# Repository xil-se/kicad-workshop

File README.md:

# Workshop example PCB

This PCB design is meant to be used as a reference for how to work with KiCad.

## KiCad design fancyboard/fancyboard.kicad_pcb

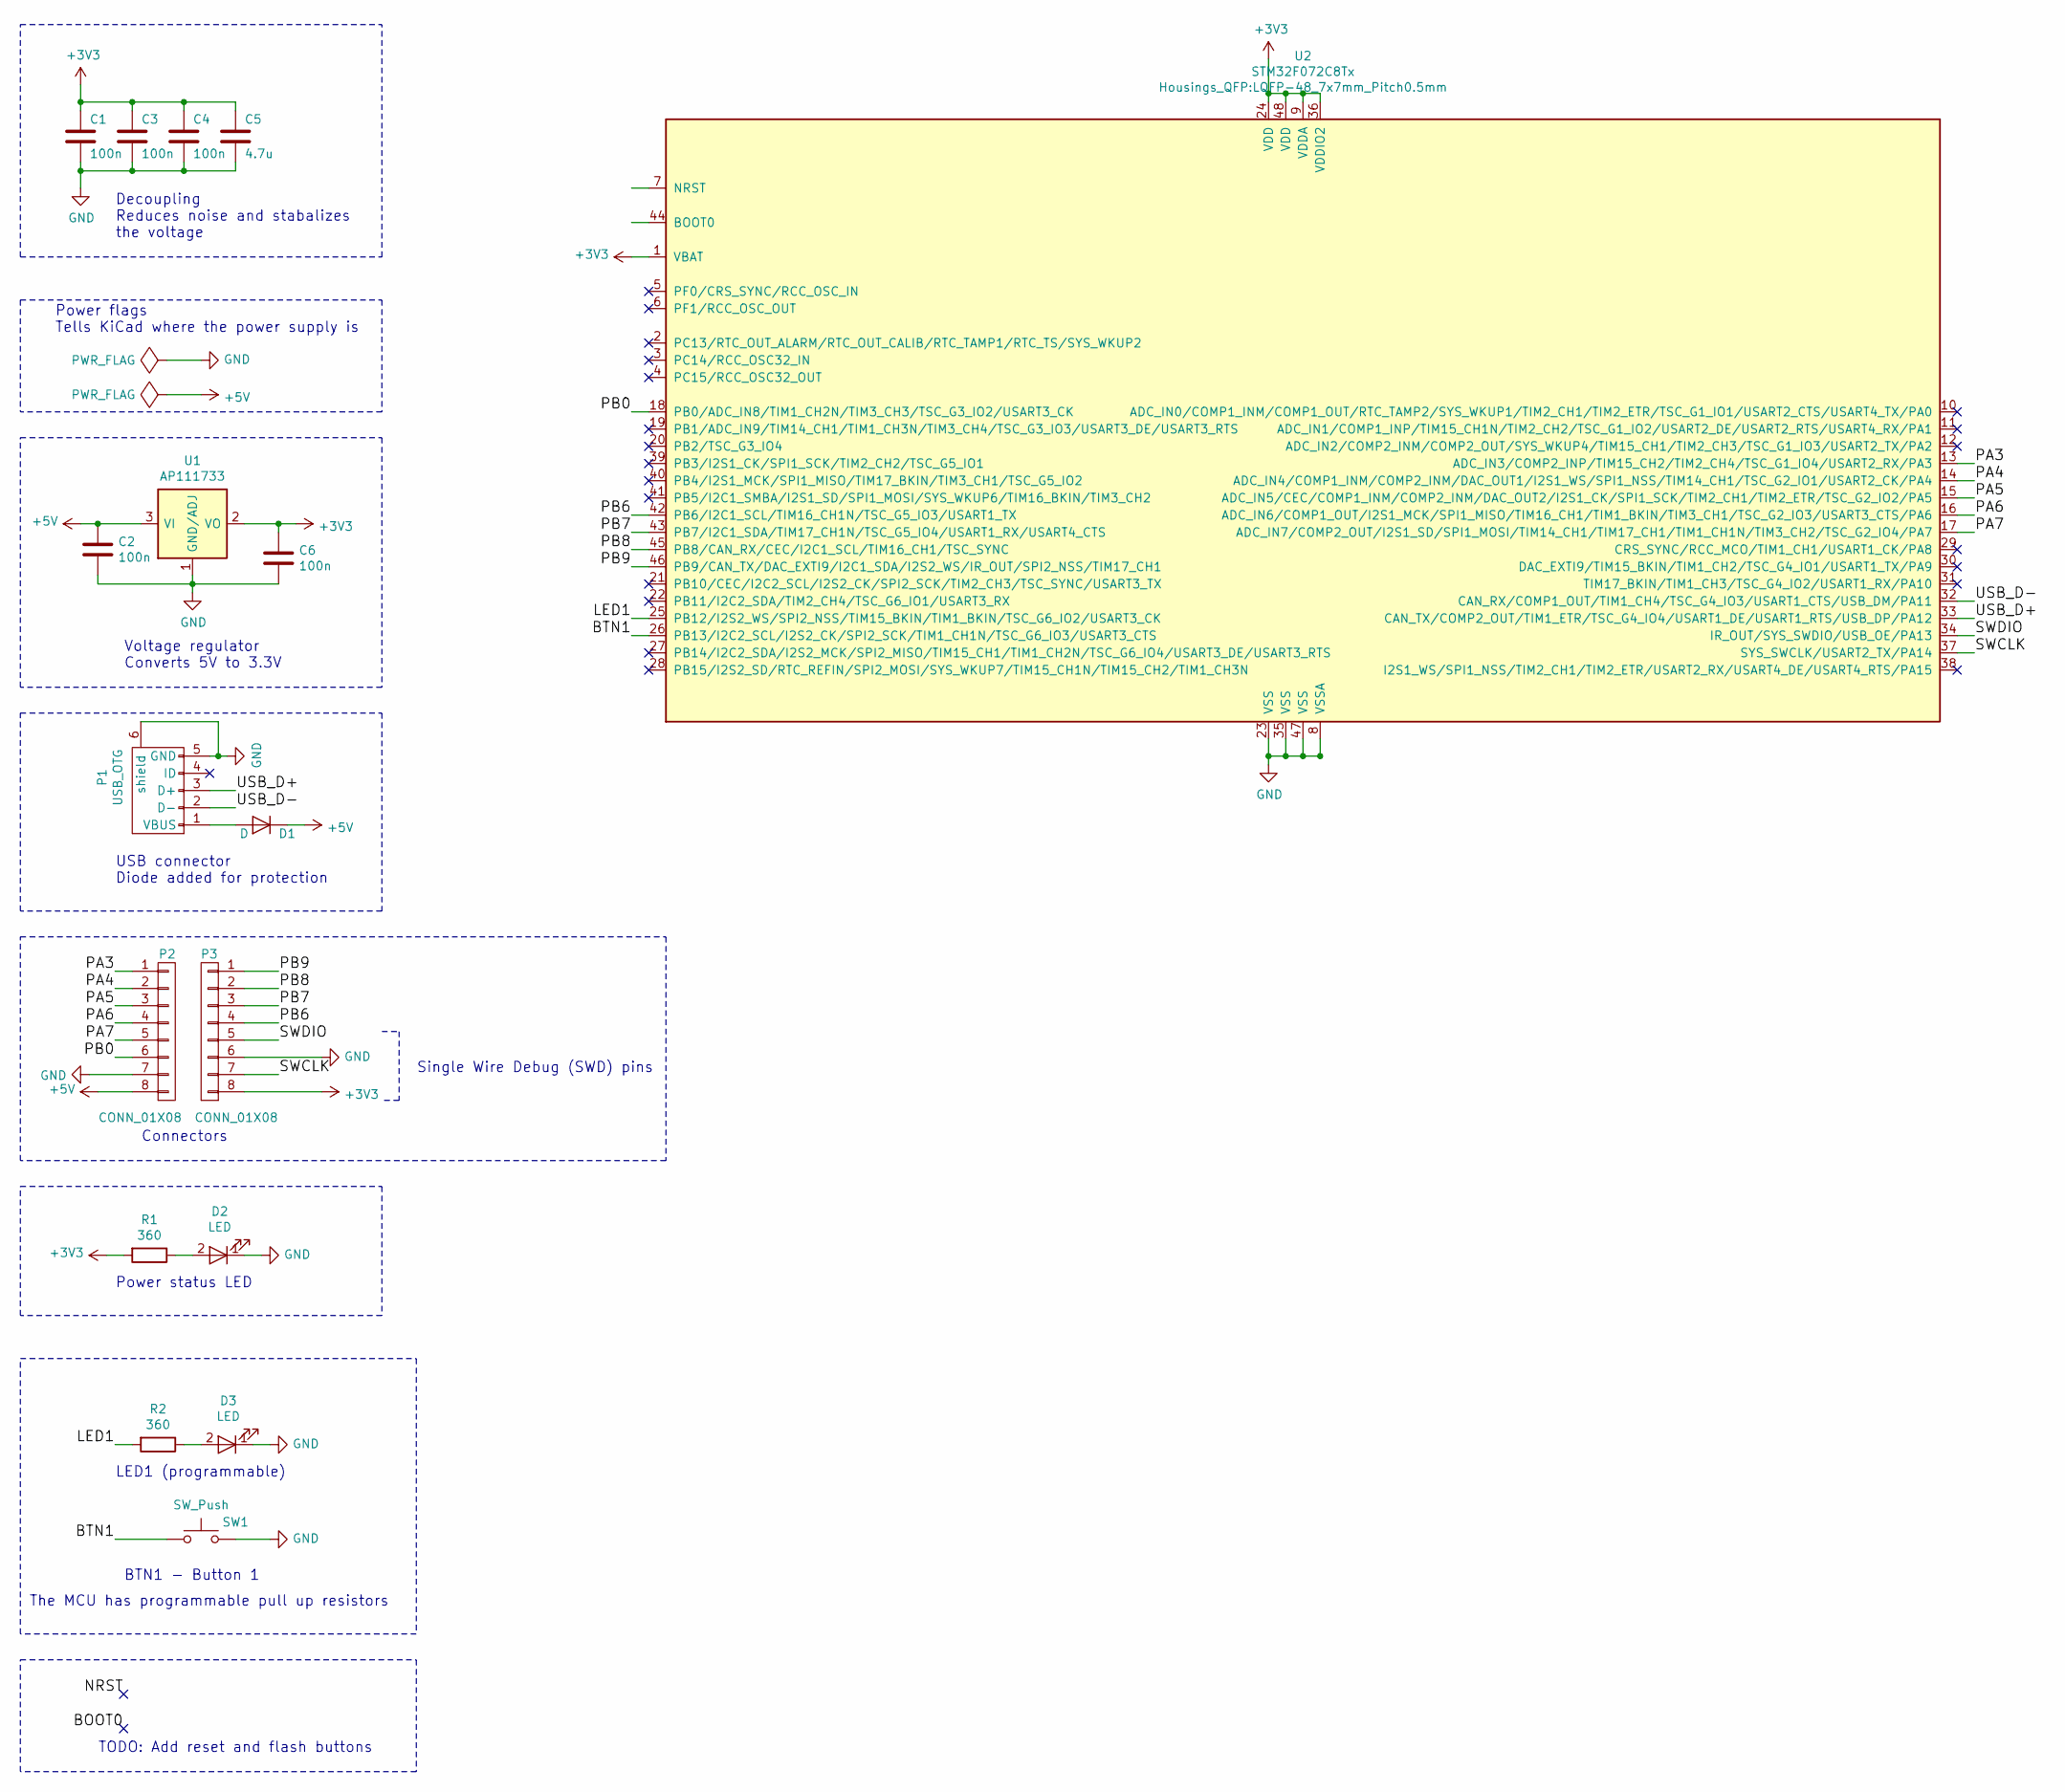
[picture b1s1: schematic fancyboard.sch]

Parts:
C1, C2, C3, C4, C6: 100n; C_0603
C5: 4.7u; C_0603
D1: D; SOD-323
D2, D3: LED; LED_0603
P1: USB_OTG; USB_Micro-B
P2, P3: CONN_01X08; Pin_Header_Straight_1x08
R1, R2: 360; R_0603
SW1: SW_Push; SmallButton
U1: AP111733; SOT-223
U2: STM32F072C8Tx; LQFP-48_7x7mm_Pitch0.5mm

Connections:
+3V3: C1.1, C3.1, C4.1, C5.1, C6.1, P3.8, R1.2, U1.2 (VO), U1.4 (VO), U2.1 (VBAT), U2.9 (VDDA), U2.24 (VDD), U2.36 (VDDIO2), U2.48 (VDD)
+5V: C2.1, D1.1 (K), P2.8, U1.3 (VI)
/BOOT0: U2.44 (BOOT0)
/BTN1: SW1.1, U2.26 (PB13/I2C2_SCL/I2S2_CK/SPI2_SCK/TIM1_CH1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)
/LED1: R2.2, U2.25 (PB12/I2S2_WS/SPI2_NSS/TIM15_BKIN/TIM1_B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)
/NRST: U2.7 (NRST)
/PA3: P2.1, U2.13 (ADC_IN3/COMP2_INP/TIM15_CH2/TIM2_CH4/TS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)
/PA4: P2.2, U2.14 (ADC_IN4/COMP1_INM/COMP2_INM/DAC_OUT1/I2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)
/PA5: P2.3, U2.15 (ADC_IN5/CEC/COMP1_INM/COMP2_INM/DAC_OUT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)
/PA6: P2.4, U2.16 (ADC_IN6/COMP1_OUT/I2S1_MCK/SPI1_MISO/TI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)
/PA7: P2.5, U2.17 (ADC_IN7/COMP2_OUT/I2S1_SD/SPI1_MOSI/TIM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)
/PB0: P2.6, U2.18 (PB0/ADC_IN8/TIM1_CH2N/TIM3_CH3/TSC_G3_I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)
/PB6: P3.4, U2.42 (PB6/I2C1_SCL/TIM16_CH1N/TSC_G5_IO3/USAR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)
/PB7: P3.3, U2.43 (PB7/I2C1_SDA/TIM17_CH1N/TSC_G5_IO4/USAR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)
/PB8: P3.2, U2.45 (PB8/CAN_RX/CEC/I2C1_SCL/TIM16_CH1/TSC_S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)
/PB9: P3.1, U2.46 (PB9/CAN_TX/DAC_EXTI9/I2C1_SDA/I2S2_WS/I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)
/SWCLK: P3.7, U2.37 (SYS_SWCLK/USART2_TX/PA14)
/SWDIO: P3.5, U2.34 (IR_OUT/SYS_SWDIO/USB_OE/PA13)
/USB_D+: P1.3 (D+), U2.33 (CAN_TX/COMP2_OUT/TIM1_ETR/TSC_G4_IO4/US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)
/USB_D-: P1.2 (D-), U2.32 (CAN_RX/COMP1_OUT/TIM1_CH4/TSC_G4_IO3/US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)
GND: C1.2, C2.2, C3.2, C4.2, C5.2, C6.2, D2.1 (K), D3.1 (K), P1.5 (GND), P1.6 (shield), P2.7, P3.6, SW1.2, U1.1 (GND/ADJ), U2.8 (VSSA), U2.23 (VSS), U2.35 (VSS), U2.47 (VSS)
unnamed: D1.2 (A), P1.1 (VBUS)
unnamed: D2.2 (A), R1.1
unnamed: D3.2 (A), R2.1

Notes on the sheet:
Decoupling Reduces noise and stabalizes the voltage
Power flags Tells KiCad where the power supply is
Voltage regulator Converts 5V to 3.3V
USB connector Diode added for protection
Connectors
Single Wire Debug (SWD) pins
Power status LED
LED1 (programmable)
BTN1 - Button 1
The MCU has programmable pull up resistors
TODO: Add reset and flash buttons

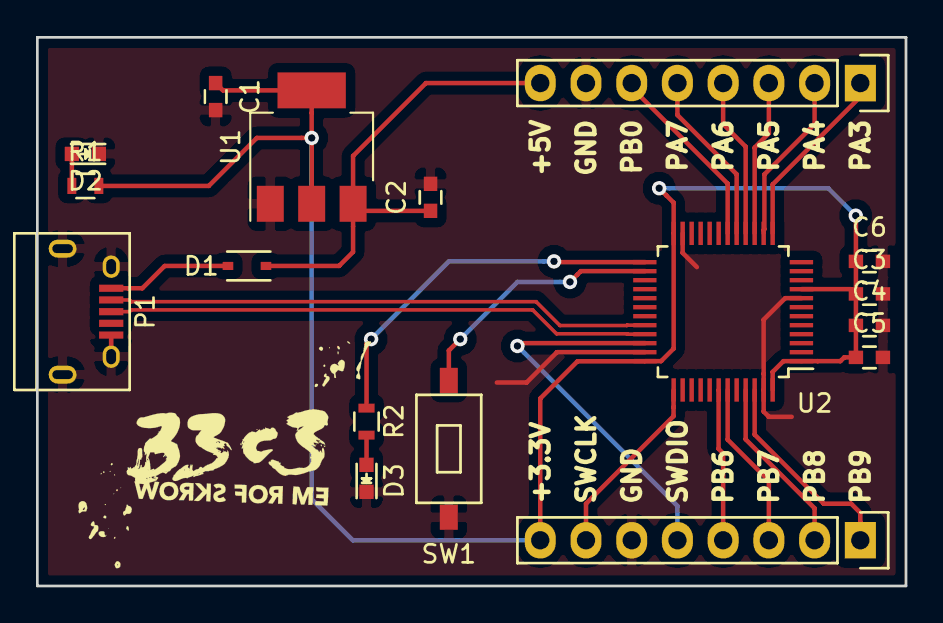
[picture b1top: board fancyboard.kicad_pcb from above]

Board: 2 copper layers, 48.3 x 30.5 mm, 17 parts (0 on the bottom side), 22 nets.

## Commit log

2016-12-27 KiCad Workshop project
2016-12-27 Support kicad-stable
    Removed diff_pair_gap and diff_pair_width configs that's been added lately.
2016-12-27 Fixed some minor issues
